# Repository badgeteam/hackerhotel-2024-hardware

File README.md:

# Hackerhotel 2024 badge

This repository contains the hardware desgin files for the Hackerhotel 2024 badge.

## License

Copyright 2024 Tilde.industries

Copyright 2024 Nicolai Electronics

This hardware design may be used under the terms of the [CERN-OHL-P](LICENSE) license.

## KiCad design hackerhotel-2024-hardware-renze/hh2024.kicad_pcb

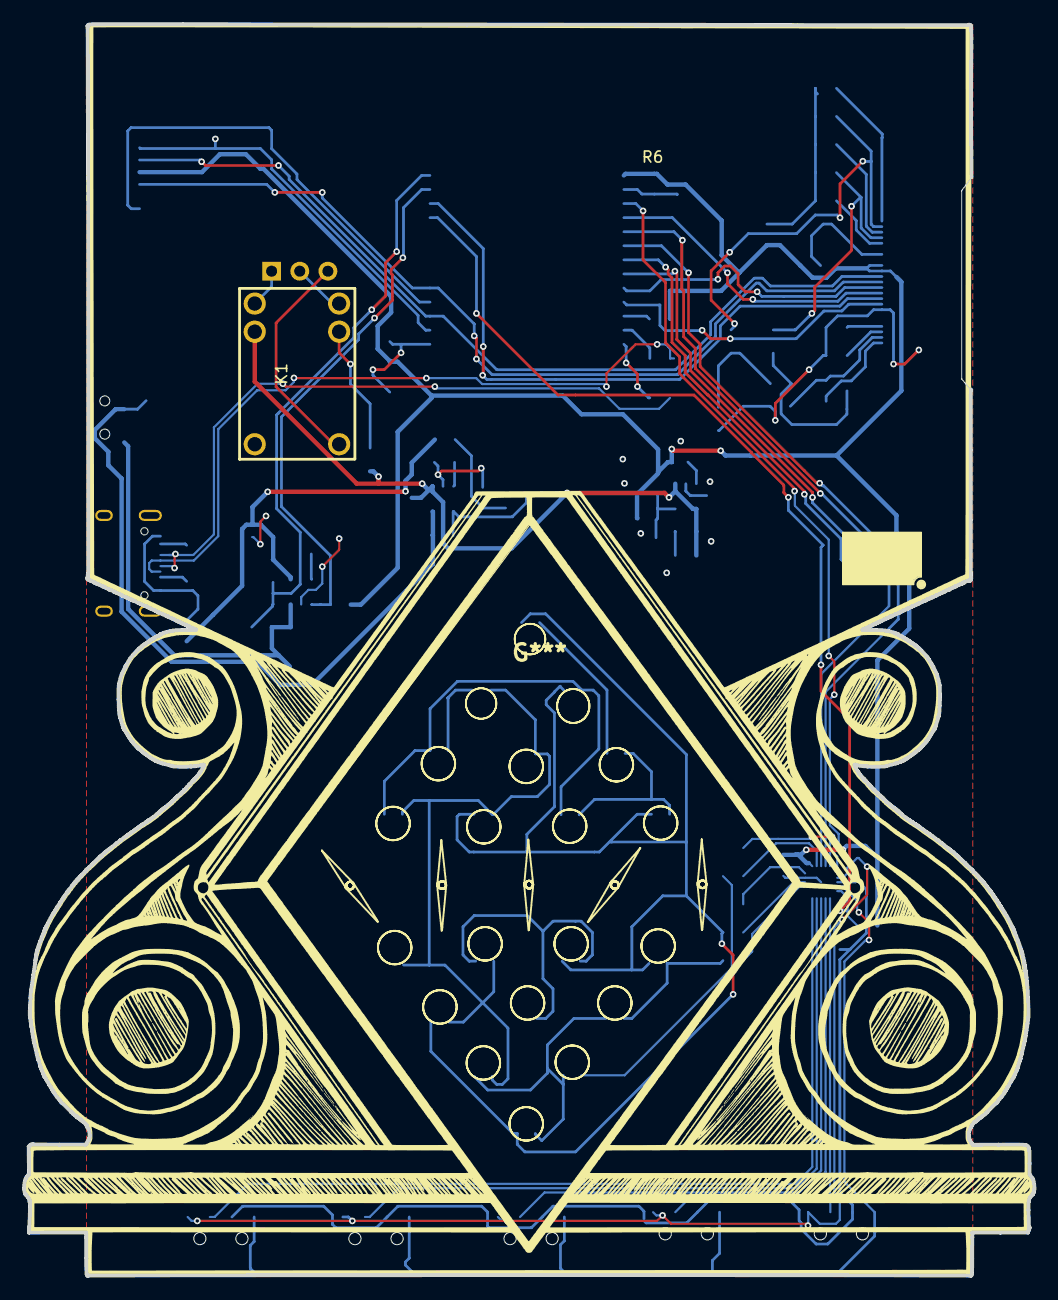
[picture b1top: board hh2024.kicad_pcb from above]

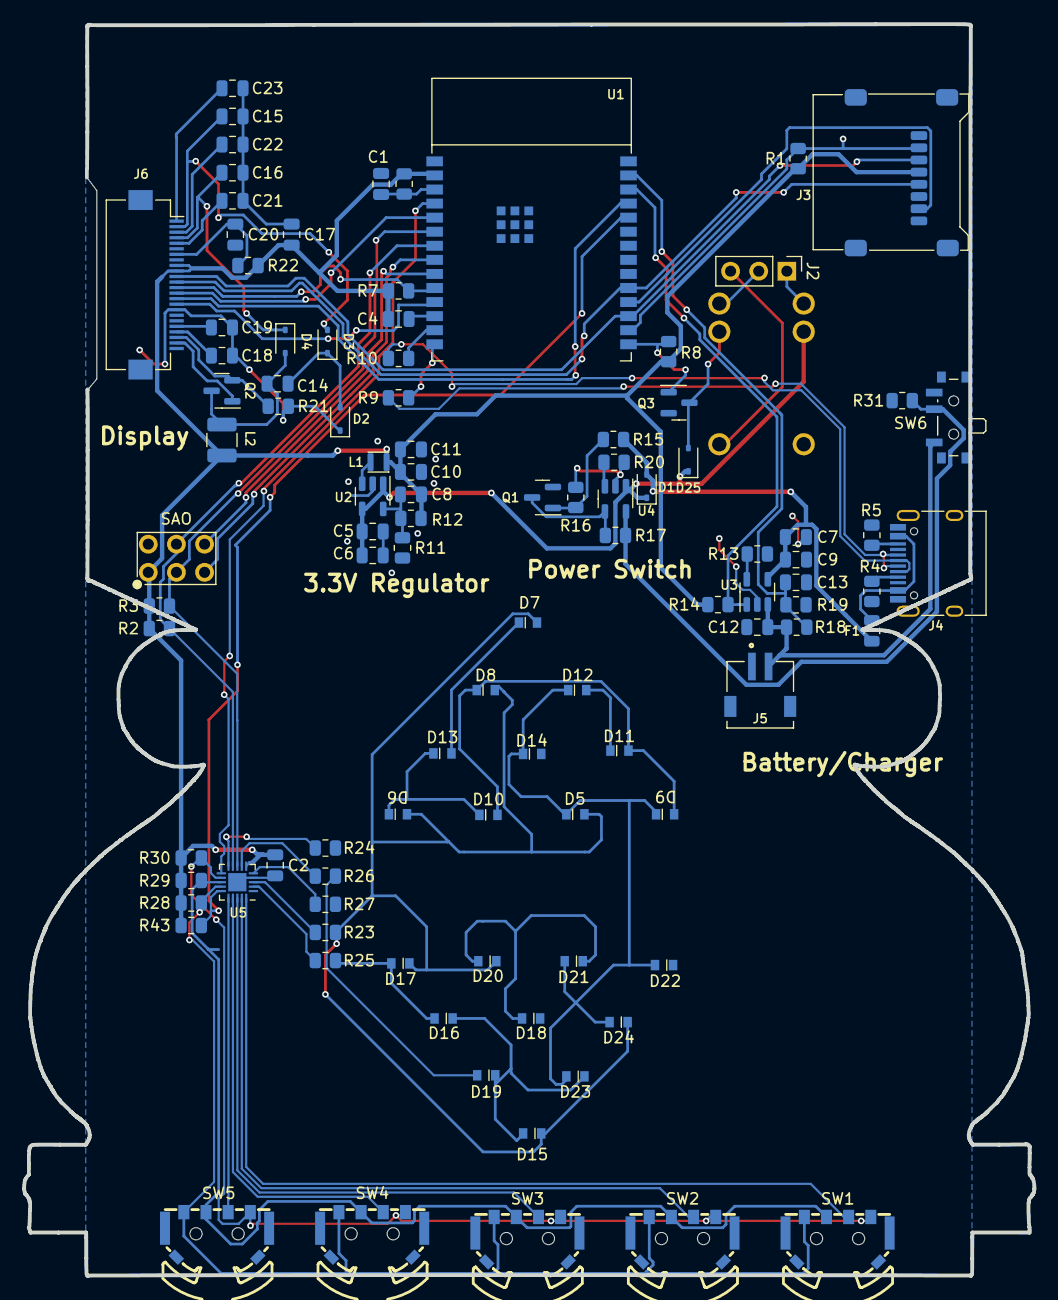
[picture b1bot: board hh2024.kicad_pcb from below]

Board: 2 copper layers, 91.2 x 113.0 mm, 103 parts (102 on the bottom side), 71 nets.

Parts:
C1, C14, C15, C16, C18, C19, C20, C21, C22, C23: 1u; C_0805_2012Metric
C2, C4, C5, C9, C13: 100n; C_0805_2012Metric
C6, C10, C11: 22u; C_0805_2012Metric
C7, C12: 10u; C_0805_2012Metric
C8: 22p; C_0805_2012Metric
C17: 4u7; C_0805_2012Metric
D1, D2, D3, D4, D25: NSVR0320MW2T1G; D_SOD-323
D5, D6, D7, D8, D9, D10, D11, D12, D13, D14, D15, D16, D17, D18, D19, D20, D21, D22, D23, D24: LED_Small; XL-1606UOC Side Sticker LED
F1: 1A; Fuse_0805_2012Metric
J1: SAO; SAO2
J2: Breakout pads; PinHeader_1x03_P2.54mm_Vertical
J3: Micro_SD_Card; MicroSD-SOFNG-TF-002-H18
J4: USB-C; USB_C_Receptacle_HRO_TYPE-C-31-M-12
J5: Battery; JST_S2B-ZR-SM4A-TF(LF)(SN)
J6: E-Paper; Hirose_FH12-24S-0.5SH_1x24-1MP_P0.50mm_Horizontal
K1: SANYOU_SRD_Form_C; HRS1H-S-DC3V
L1: 2.2u; Inductor_MSC20FC
L2: 47u; L_1210_3225Metric
Q1, Q2, Q3: AP2302B; SOT-23
R1, R6, R7, R8, R11, R14, R17, R28, R29, R30, R43: 10k; R_0805_2012Metric
R2, R3: 4k7; R_0805_2012Metric
R4, R5: 5.1k; R_0805_2012Metric
R9, R10, R21: 27; R_0805_2012Metric
R12: 45.3k; R_0805_2012Metric
R13: 2k; R_0805_2012Metric
R15: 1k; R_0805_2012Metric
R16, R18, R19, R31: 100k; R_0805_2012Metric
R20: 4.7k; R_0805_2012Metric
R22: 0; R_0805_2012Metric
R23, R24, R25, R26, R27: 30; R_0805_2012Metric
SW1, SW2, SW3, SW4, SW5: Multi-Directional-Switches; TM-2023
SW6: SW_SPDT; SW_SPDT_PCM12
U1: ESP32-C6-WROOM-1
U2: SY8079AAC; SOT-23-5
U3: XT4054K421MR-G; SOT-23-5
U4: SY6280AAC; SOT-23-5
U5: CH32V003F4U6; QFN-20-1EP_3x3mm_P0.4mm_EP1.65x1.65mm

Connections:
+3V3: C2.2, C4.1, C8.1, C10.1, C11.1, C17.2, J1.1 (+3.3V), J3.4 (VDD), J6.9, J6.10, L1.1, L2.1, R1.1, R2.2, R3.2, R6.2, R7.2, R8.1, R12.1, R14.2, R22.1, R28.1, R29.1, R30.1, R43.1, U1.2 (3V3), U5.6 (VDD)
/A: D5.1 (K), D9.1 (K), D12.1 (K), D14.1 (K), D21.2 (A), D22.2 (A), D23.2 (A), D24.2 (A), R27.2
/B: D6.1 (K), D10.1 (K), D13.1 (K), D14.2 (A), D18.2 (A), D19.2 (A), D20.2 (A), D21.1 (K), R26.2
/C: D7.1 (K), D11.1 (K), D12.2 (A), D13.2 (A), D16.2 (A), D17.2 (A), D18.1 (K), D22.1 (K), R25.2
/CC1: J4.A5 (CC1), R4.2
/CC2: J4.B5 (CC2), R5.2
/D: D8.1 (K), D9.2 (A), D10.2 (A), D11.2 (A), D15.2 (A), D16.1 (K), D19.1 (K), D23.1 (K), R24.2
/E: D5.2 (A), D6.2 (A), D7.2 (A), D8.2 (A), D15.1 (K), D17.1 (K), D20.1 (K), D24.1 (K), R23.2
/E-Paper/BUSY: J6.16, U1.11 (GPIO10)
/E-Paper/CS: J6.13, R7.1, U1.10 (GPIO8)
/E-Paper/DC: J6.14, U1.5 (MTDI/GPIO5/ADC1_CH5)
/E-Paper/GDR: J6.23, Q2.1 (G)
/E-Paper/MOSI: J3.3 (CMD), J6.11, U1.17 (GPIO19)
/E-Paper/PREVGH: C16.2, D4.1 (K), J6.4
/E-Paper/PREVGL: C15.1, D3.2 (A), J6.2
/E-Paper/RESE: J6.22, Q2.2 (S), R21.2
/E-Paper/RESET: J6.15, U1.25 (U0TXD/GPIO16)
/E-Paper/SCK: J3.5 (CLK), J6.12, U1.19 (GPIO21)
/E-Paper/VCOM: C23.2, J6.1
/E-Paper/VGH: C19.2, J6.20
/E-Paper/VGL: C18.2, J6.21
/E-Paper/VSH: C21.2, J6.5
/E-Paper/VSL: C22.2, J6.3
/Power management/CHRG: R14.1, U1.26 (GPIO3/ADC1_CH3), U3.1 (STAT)
/Power management/FB33: C8.2, R11.1, R12.2, U2.5 (FB)
/Power management/SENSE: C13.1, R18.1, R19.2, U1.27 (GPIO2/ADC1_CH2)
/Power management/SW33: L1.2, U2.3 (SW)
/USB_VBUS: F1.2, J4.A4 (VBUS), J4.A9 (VBUS), J4.B4 (VBUS), J4.B9 (VBUS)
/microcontroller/CH32 Prog: R43.2, U1.24 (U0RXD/GPIO17), U5.15 (PD1)
/microcontroller/D+: J4.A6 (D+), J4.B6 (D+), R9.1
/microcontroller/D-: J4.A7 (D-), J4.B7 (D-), R10.1
/microcontroller/Low Pow CH32: U1.4 (MTMS/GPIO4/ADC1_CH4), U5.11 (PC4)
/microcontroller/Relay Ctrl: Q3.1 (G), R8.2, U1.15 (GPIO9)
/microcontroller/SAO IO1: J1.5 (IO1), U1.8 (GPIO0/ADC1_CH0/XTAL_32K_P)
/microcontroller/SAO IO2: J1.6 (IO2), U1.9 (GPIO1/ADC1_CH1/XTAL_32K_N)
/microcontroller/SDCARD CS: J3.2 (DAT3/CD), R1.2, U1.16 (GPIO18)
/microcontroller/SPI MISO: J3.7 (DAT0), U1.18 (GPIO20)
GND: C1.2, C2.1, C4.2, C5.2, C6.2, C7.1, C9.1, C10.2, C11.2, C12.2, C13.2, C15.2, C16.1, C17.1, C18.1, C19.1, C20.1, C21.1, C22.1, C23.1, D2.1 (K), J1.2 (GND), J3.6 (VSS), J3.9 (SHIELD), J4.A1 (GND), J4.A12 (GND), J4.B1 (GND), J4.B12 (GND), J4.S1 (SHIELD), J5.1, J5.MP (MountPin), J6.8, J6.17, J6.MP (MountPin), Q1.2 (S), Q3.2 (S), R4.1, R5.1, R11.2, R13.1, R16.1, R19.1, R20.1, R21.1, R31.1, U1.1 (GND), U1.12 (GPIO11), U1.28 (GND), U1.29 (GND), U2.2 (GND), U3.2 (VSS), U4.2 (GND), U5.4 (VSS), U5.21 (VSS)
LED A: R27.1, U5.5 (PD0)
LED B: R26.1, U5.7 (PC0)
LED C: R25.1, U5.2 (PA1)
LED D: R24.1, U5.10 (PC3)
LED E: R23.1, U5.3 (PA2)
MSWB: R29.2, SW1.T, SW2.T, SW3.T, SW4.T, SW5.T, U5.13 (PC6)
MSWL: R28.2, SW1.2, SW2.2, SW3.2, SW4.2, SW5.2, U5.14 (PC7)
MSWR: R30.2, SW1.1, SW2.1, SW3.1, SW4.1, SW5.1, U5.12 (PC5)
MSWS1: SW1.C, U5.20 (PD6)
MSWS2: SW2.C, U5.19 (PD5)
MSWS3: SW3.C, U5.18 (PD4)
MSWS4: SW4.C, U5.17 (PD3)
MSWS5: SW5.C, U5.16 (PD2)
unnamed: C14.1, D2.2 (A), D3.1 (K)
unnamed: C14.2, D4.2 (A), L2.2, Q2.3 (D)
unnamed: D25.2 (A), K1.2, Q3.3 (D)
unnamed: J2.1, K1.4
unnamed: J2.2, K1.3
unnamed: J2.3, K1.1
unnamed: C20.2, J6.7, R22.2
unnamed: Q1.3 (D), R17.2, U4.4 (ON)
unnamed: Q1.1 (G), R15.2, R16.2
unnamed: R17.1, R31.2, SW6.2 (B), U4.5 (IN)
unnamed: C1.1, R6.1, U1.3 (EN/CHIP_PU)
unnamed: R10.2, U1.13 (GPIO12/USB_D-)
unnamed: R9.2, U1.14 (GPIO13/USB_D+)
unnamed: R13.2, U3.5 (PROG)
unnamed: R20.2, U4.3 (SET)
SCL: J1.4 (SCL), R2.1, U1.7 (MTDO/GPIO7), U5.9 (PC2)
SDA: J1.3 (SDA), R3.1, U1.6 (MTCK/GPIO6/ADC1_CH6), U5.8 (PC1)
VBAT: C12.1, J5.2, R18.2, SW6.1 (A), U3.3 (VBAT)
VIN: C5.1, C6.1, D1.1 (K), D25.1 (K), K1.5, U2.1 (EN), U2.4 (VIN), U4.1 (OUT)
VUSB: C7.2, C9.2, D1.2 (A), F1.1, R15.1, U3.4 (VDD)

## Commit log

2023-06-13 First commit with empty project
2023-06-15 Added the rest of the components
2023-06-16 Add USB-C, Power regulator and the basics for the RP2040
2023-06-16 Add usb hub and wireup the usb ports
2023-06-16 Add a part reference
2023-10-12 V1 of schematic
2023-10-12 V1.1 schematic
    Added a relay for clicking noise
    Multiplexed the switches and moved them all to the CH32
    Wired an ESP32 low power triggered pin (GPIO4) to PC4 on the CH32 so it can wake it up on input change
2023-10-12 V1.1 Continued
    Added a pull up on CH32 prog
2023-10-13 Started layout
2023-10-14 removed extra pull ups on multi switches
2023-10-15 Routing complete (apart from LEDs)
2023-10-16 routing almost finished
2023-10-17 Added artwork + more routing
2023-10-18 Routing and BOM completed, missing art and regulator update
2023-10-20 V1 complete
2023-10-21 Fixed the soldermask under the LEDs
2023-11-26 before tidy
2023-11-26 After tidy
2023-11-29 Annoted schematic with letters for LEDs
2023-12-03 V1.1 almost complete update
    ✔️add a 100k resistor between the gate of the FET in the epaper circuit and ground
    ✔️Moved LEDs to match the alignment on line “HIKL” and “Y”
    ✔️Change polarity on the LEDs, they are the “wrong way around” (software thing only, doesn’t matter for charlieplexing
    -Add relay control on PD7 (if it can be changed)
    ✔️Swap PA1 and PA2 with PD3 and PD2
    ✔️ Prog pads for CH32
2023-12-05 V1.2
    added reverse mount RGB LED
2023-12-05 Added battery cycle ch/dis curve
2023-12-10 generated gerbers
2023-12-10 V1.3
    Moved routing of CH32 top layer tracks
    Moved SD card inward
    added keepout on relay
2023-12-12 V1.3
    Changed C23 from 1uF to 0.47uF
    Changed R21 from 27ohms to 2.2ohms
    Changed C17 from 4.7uF to 1uF
    Removed R37 and R38, R39 and R40
    Added J2 QWIIC connector
    Added U6 buffer to drive SK6085 LED
2023-12-13 removed connection from LEDs to CH32
2023-12-13 Fixed the sao ヽ༼ ツ ༽ﾉ
    and some routing
2023-12-15 Small fixes and change footprint library for missing libraries
2023-12-16 Fix power circuit, add headers and move stuff
2023-12-16 Added art, first pass without DRC
2023-12-16 Added artwork (cont)
    DRC pass
    Removed header from the BoM
    changed the relay header to SMD so it doesn't clash with art
    made header for CH32 prog THT
    Moved designators in reasonable place
    added hacker hotel and badge.team artwork
2023-12-16 updated artwork
2023-12-16 Update fp-info-cache
2023-12-16 updated the switched and routing around it
2023-12-17 Moar headers
2023-12-17 tidy silk and solved DRC errors
2023-12-17 V1.4
    Swapped back PA1 and PA2 with PD3 and PD2 since Renze got them working
    7 errors of copper which bleeds over edgecut
    117 warning of soldermask bridging
    generated bom, gerber, placement files and schematic
2023-12-17 updated the f.mask art and moved 2 tracks
2023-12-17 fixed a copper not fully filled in the diamond
2024-03-01 Add readme & license
2024-03-01 Remove unused file
2024-03-01 Fix readme
